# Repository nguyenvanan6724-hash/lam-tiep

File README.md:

# ESP32-C6 audio recorder

| Thư mục / file | Nội dung |
|---|---|
| [`esp32c6_recorder_revC2/`](esp32c6_recorder_revC2/) | **Bản mới nhất.** PCB layout lại 60 × 46 mm, 2 lớp, GND liền lớp dưới. Đọc [README](esp32c6_recorder_revC2/README.md) trước. |
| [`esp32c6_recorder_revC1_goc/`](esp32c6_recorder_revC1_goc/) | Bản gốc rev C1, giữ nguyên để so sánh |
| `Review_schematic_ESP32-C6 (1).pdf`, `esp32_c6_project.pdf` | Tài liệu cũ (review schematic bản trước, bản in schematic cũ) |

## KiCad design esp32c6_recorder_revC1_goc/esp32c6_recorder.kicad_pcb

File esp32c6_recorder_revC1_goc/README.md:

# ESP32-C6 audio recorder – project KiCad 10 (rev C)

Mở `esp32c6_recorder.kicad_pro` bằng KiCad 10 → mở Schematic → **chạy ERC trước** → *Tools → Update PCB from Schematic* (F8).

## Rev C thay đổi gì so với rev B

- **Bỏ CH340C (U11) + mạch tự reset (Q4, Q5, R53–R56, C36, C37).** Nạp code và xem log bằng khối USB Serial/JTAG có sẵn trong ESP32-C6.
- USB-C D+/D− → R70/R71 (22 Ω) → GPIO13/GPIO12. Có chừa chỗ C44/C45 xuống GND (KHÔNG hàn), theo khuyến nghị của Espressif.
- Thẻ SD dời khỏi GPIO12/13: **SD_SCK → GPIO18** (qua R62), **SD_MISO → GPIO19**. SD_CS (IO10) và SD_MOSI (IO11) giữ nguyên.
- UART0 (GPIO16/17) để trống (có cờ no-connect).
- Mọi linh kiện có thêm trường `MPN` và `LCSC` (mã LCSC đã kiểm còn hàng ngày 04/11/2026).
- Net class `USB` có thêm `USB_DP_MCU`, `USB_DM_MCU`.

## Firmware cần chỉnh

- ESP-IDF: `idf.py menuconfig` → Component config → ESP System Settings → Channel for console output = **USB Serial/JTAG**.
- Arduino: Tools → **USB CDC On Boot: Enabled**.
- Firmware treo, ngủ sâu, hoặc lấy IO12/IO13 làm GPIO thì cổng USB sẽ mất. Cách nạp lại: **giữ BOOT, bấm RESET, thả BOOT** để chip vào ROM download, cổng USB sẽ hiện lại.

## File trong project

| File | Nội dung |
|---|---|
| `esp32c6_recorder.kicad_sch` | Schematic rev C (A2) |
| `bom.csv` | BOM gộp: footprint, MPN, **mã LCSC, giá "từ", tồn kho, link** |
| `lib/esp32c6_rec.kicad_sym` | Symbol riêng (vẫn còn symbol CH340C trong thư viện, schematic không dùng nữa) |
| `lib/esp32c6_rec.pretty/` | Footprint riêng: ESP32-C6-WROOM-1, TPS63802 (DLA0010A) |
| `schematic_rev_B_cu.pdf`, `erc_rev_B_cu.rpt` | Bản in và kết quả ERC của **rev B cũ**, giữ lại để so sánh |

## Phải tự kiểm tra

1. **ERC trong KiCad 10.** Rev C được sửa trực tiếp trong file schematic, chưa mở bằng KiCad. Tao đã tự kiểm netlist bằng script (chỉ đổi đúng các net dự kiến, không có dây treo hay nhãn lạc), nhưng vẫn phải chạy ERC thật.
2. In PDF rev C mới: File → Plot.
3. L2: mã mua là Murata **DFE201612E**-R47M, còn footprint đang gán là **DFE201610P**. Hai loại cùng thân 2.0×1.6 mm, nhưng phải so land pattern trong datasheet Murata trước khi đặt PCB.
4. Footprint TPS63802 do Claude tự vẽ theo DLA0010A (TI SLVSEU9D). In tỉ lệ 1:1 và so lại.
5. Khoảng cách 2 hàng chân module INMP441 (J8/J9, J10/J11) phải đo trên module thật.
6. LED 0603: dấu cực tính trên LED LCSC mỗi hãng một kiểu, xem datasheet trước khi hàn.

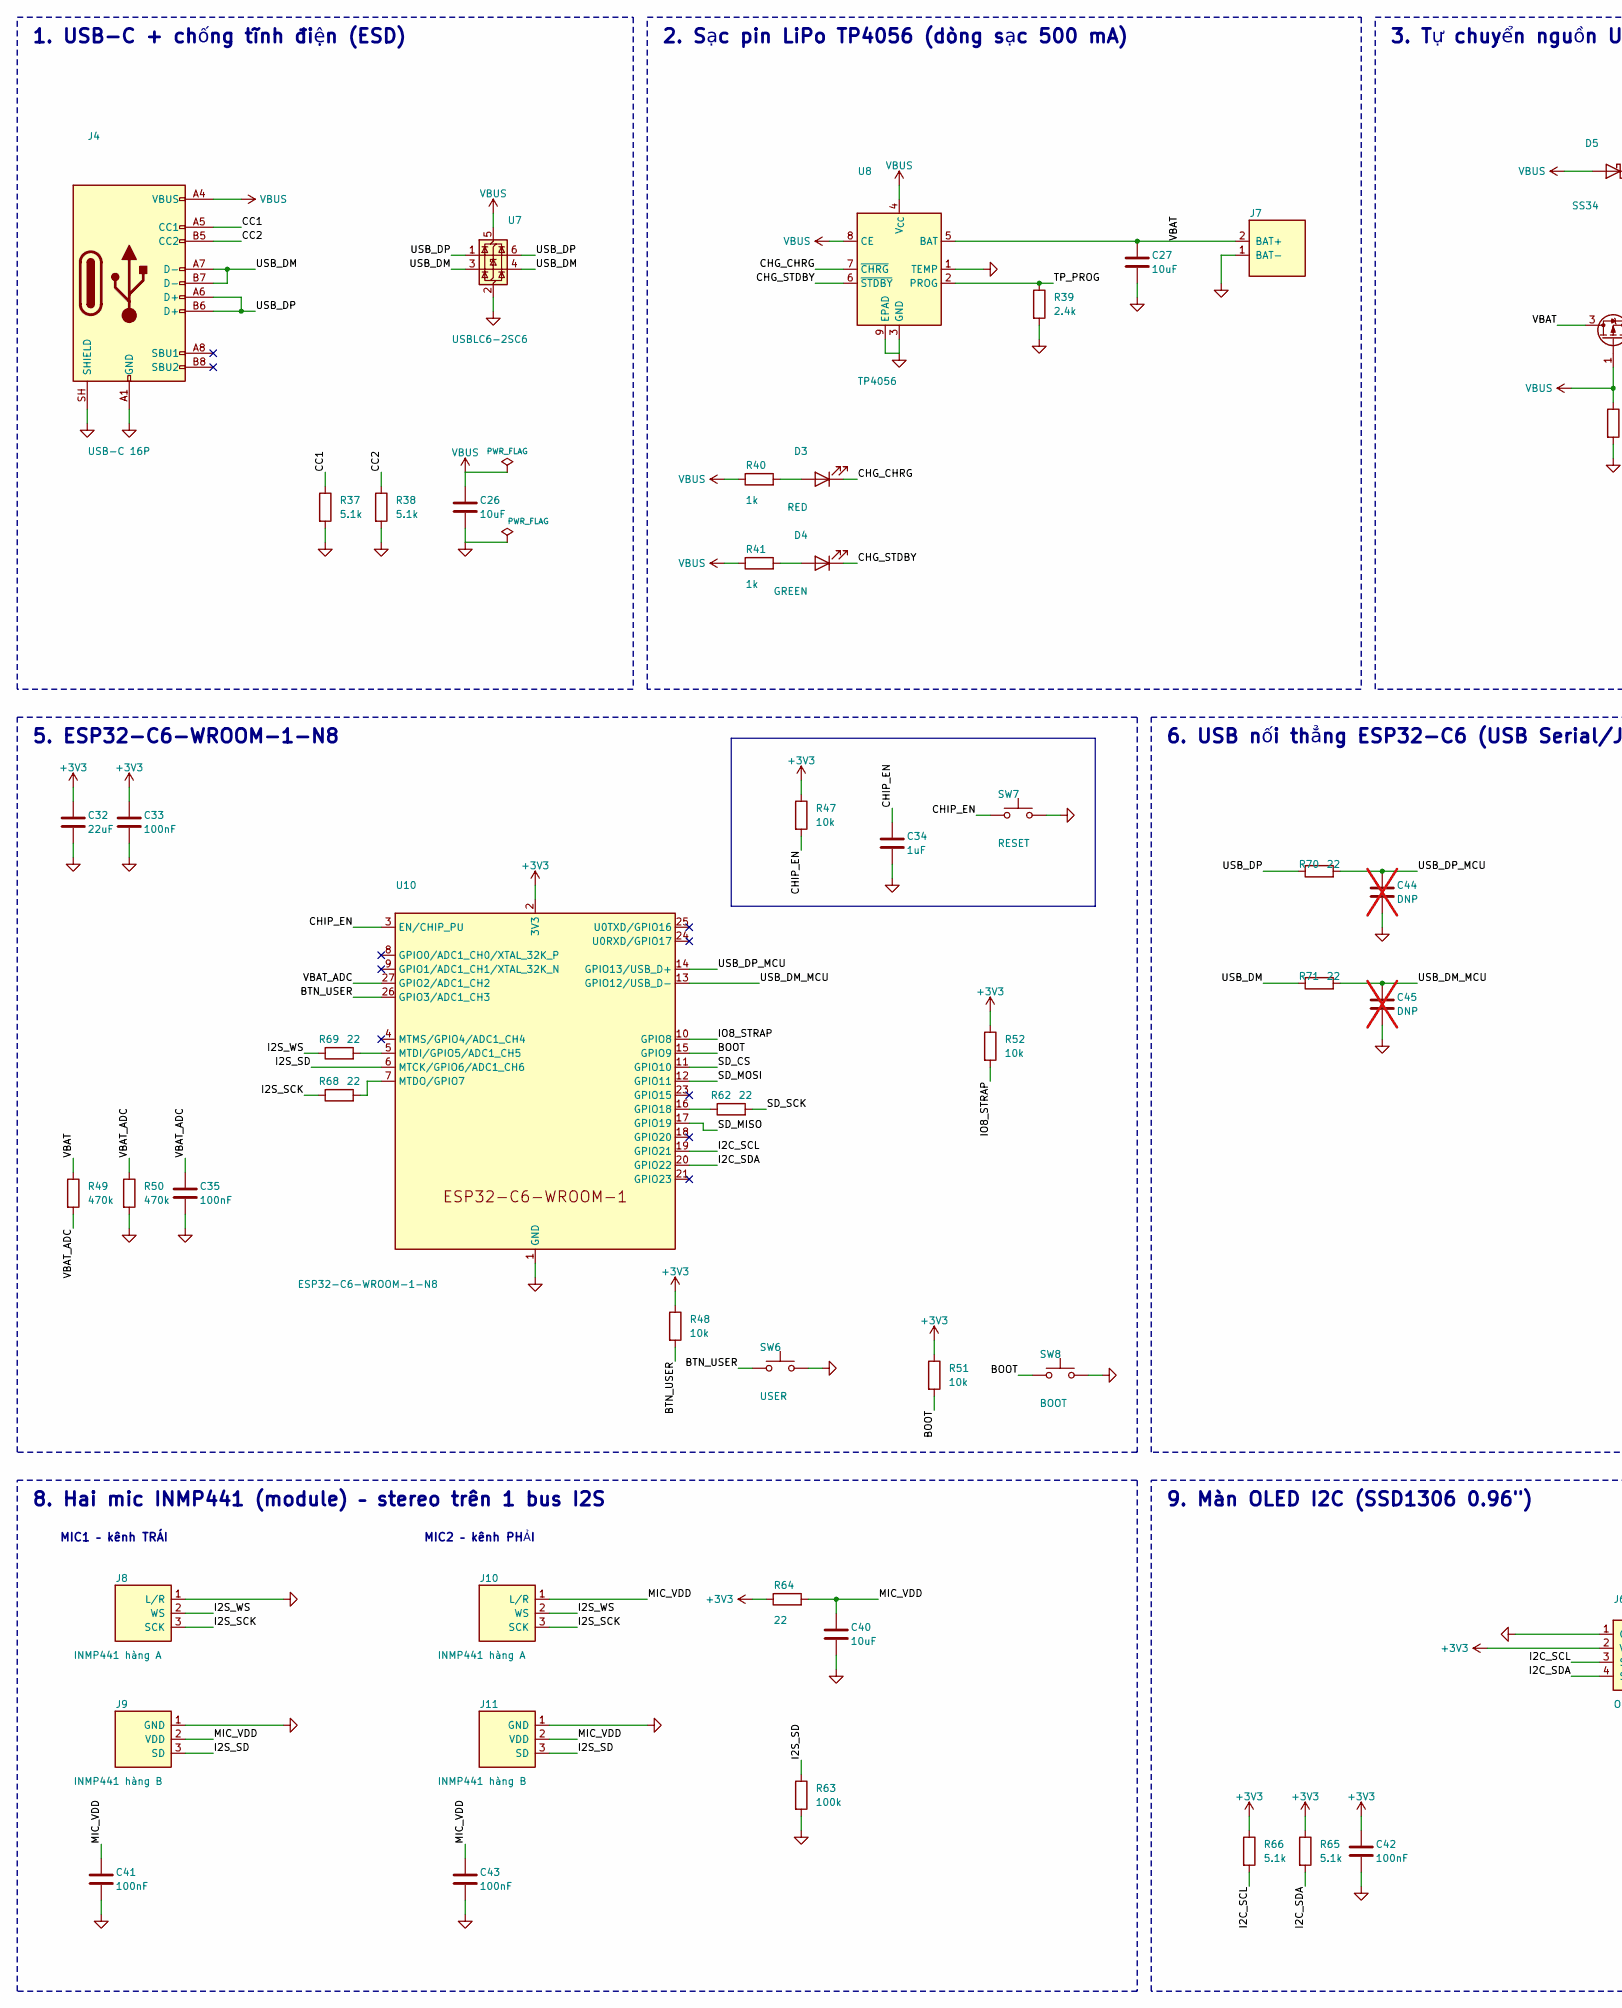
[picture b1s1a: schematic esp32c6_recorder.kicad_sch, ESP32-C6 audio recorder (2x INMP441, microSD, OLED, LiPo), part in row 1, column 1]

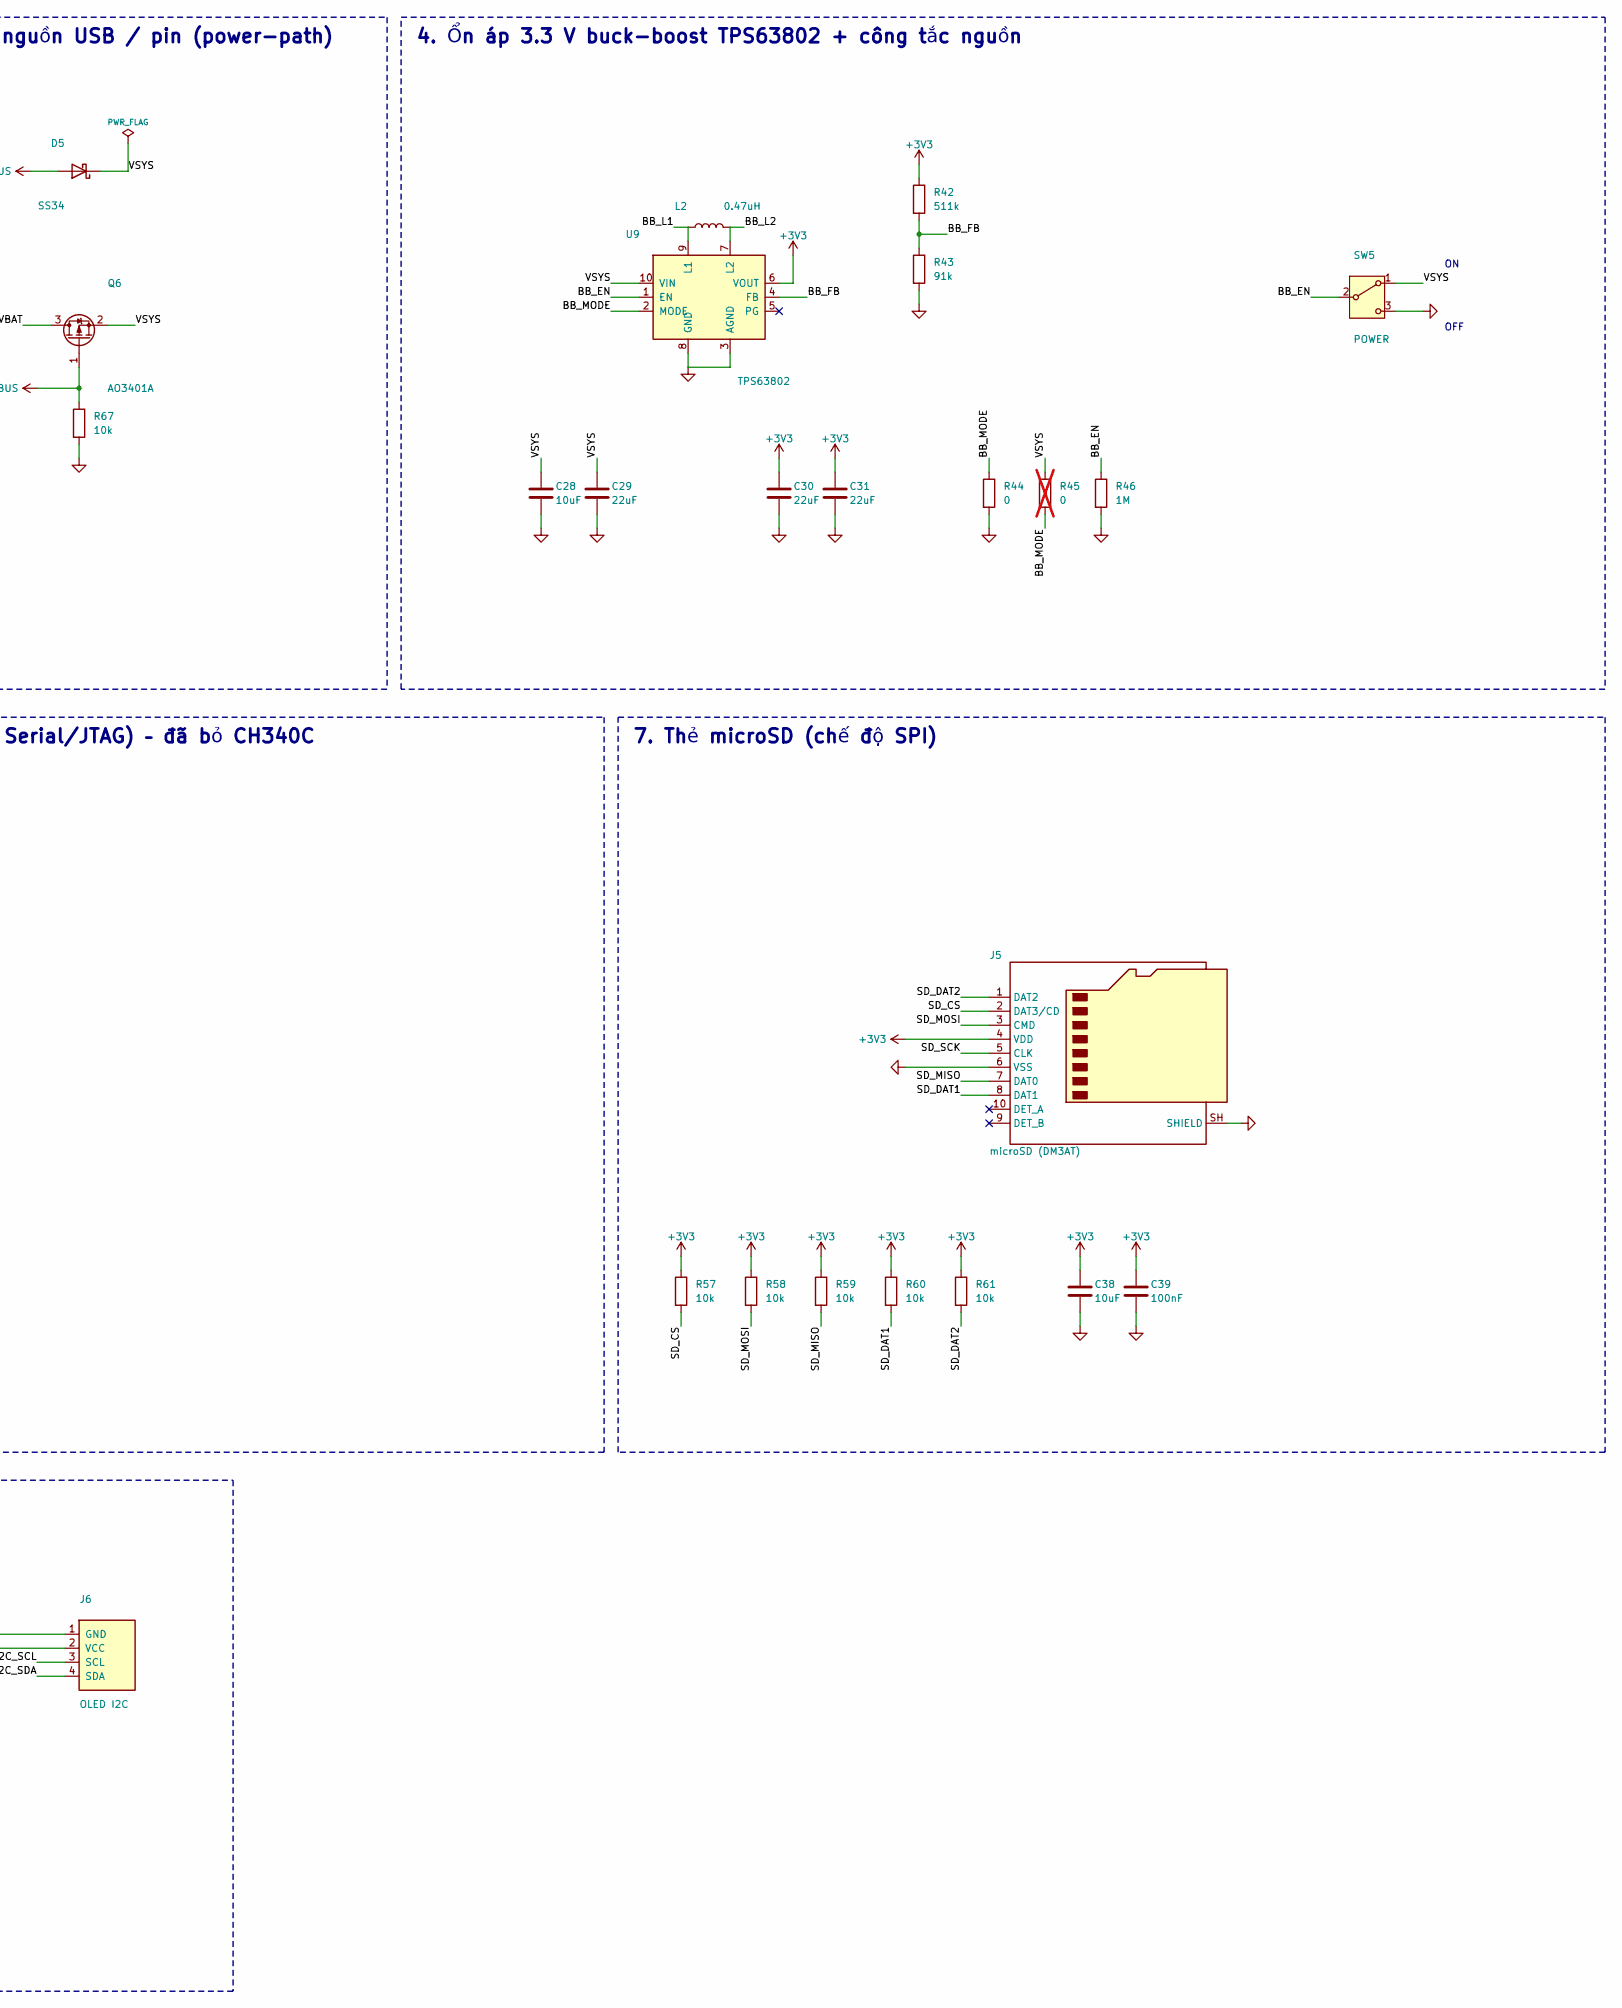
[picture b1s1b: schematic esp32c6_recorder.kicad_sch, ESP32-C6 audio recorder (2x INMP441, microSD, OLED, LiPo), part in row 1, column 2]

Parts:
C26, C27, C38, C40: 10uF; C_0805_2012Metric; MPN Samsung CL21A106KAYNNNE; LCSC C15850
C28: 10uF; C_0603_1608Metric; MPN Samsung CL10A106KP8NNNC; LCSC C19702
C29, C32: 22uF; C_0805_2012Metric; MPN Samsung CL21A226MPQNNNE; LCSC C29277
C30, C31: 22uF; C_0603_1608Metric; MPN Murata GRM188R61A226ME15D; LCSC C84419
C33, C35, C39, C41, C42, C43: 100nF; C_0603_1608Metric; MPN Samsung CL10B104KB8NNNC; LCSC C1591
C34: 1uF; C_0603_1608Metric; MPN Samsung CL10A105KB8NNNC; LCSC C15849
C44, C45: DNP; C_0603_1608Metric; not fitted
D3: RED; LED_0603_1608Metric; MPN KENTO KT-0603R; LCSC C2286
D4: GREEN; LED_0603_1608Metric; MPN KENTO KT-0603G; LCSC C12624
D5: SS34; D_SMA; MPN MDD SS34; LCSC C8678
J4: USB-C 16P; USB_C_Receptacle_HRO_TYPE-C-31-M-12; MPN HRO TYPE-C-31-M-12; LCSC C165948
J5: microSD (DM3AT); microSD_HC_Hirose_DM3AT-SF-PEJM5; MPN Hirose DM3AT-SF-PEJM5; LCSC C114218
J6: OLED I2C; PinSocket_1x04_P2.54mm_Vertical; MPN BOOMELE 2.54-1*4P (header cái); LCSC C2718488
J7: LiPo 1S (có PCM); JST_PH_S2B-PH-K_1x02_P2.00mm_Horizontal; MPN JST S2B-PH-K-S(LF)(SN); LCSC C173752
J8, J10: INMP441 hàng A; PinSocket_1x03_P2.54mm_Vertical; MPN BOOMELE 2.54-1*3P (header cái); LCSC C146243
J9, J11: INMP441 hàng B; PinSocket_1x03_P2.54mm_Vertical; MPN BOOMELE 2.54-1*3P (header cái); LCSC C146243
L2: 0.47uH; L_Murata_DFE201610P; MPN Murata DFE201612E-R47M=P2; LCSC C668312
Q6: AO3401A; SOT-23; MPN AOS AO3401A; LCSC C15127
R37, R38, R65, R66: 5.1k; R_0603_1608Metric; MPN UNI-ROYAL 0603WAF5101T5E; LCSC C23186
R39: 2.4k; R_0603_1608Metric; MPN UNI-ROYAL 0603WAF2401T5E; LCSC C22940
R40, R41: 1k; R_0603_1608Metric; MPN UNI-ROYAL 0603WAF1001T5E; LCSC C21190
R42: 511k; R_0603_1608Metric; MPN UNI-ROYAL 0603WAF5113T5E; LCSC C23194
R43: 91k; R_0603_1608Metric; MPN UNI-ROYAL 0603WAF9102T5E; LCSC C23265
R44: 0; R_0603_1608Metric; MPN UNI-ROYAL 0603WAF0000T5E; LCSC C21189
R45: 0; R_0603_1608Metric; MPN UNI-ROYAL 0603WAF0000T5E; LCSC C21189; not fitted
R46: 1M; R_0603_1608Metric; MPN UNI-ROYAL 0603WAF1004T5E; LCSC C22935
R47, R48, R51, R52, R57, R58, R59, R60, R61, R67: 10k; R_0603_1608Metric; MPN UNI-ROYAL 0603WAF1002T5E; LCSC C25804
R49, R50: 470k; R_0603_1608Metric; MPN UNI-ROYAL 0603WAF4703T5E; LCSC C23178
R62, R64, R68, R69, R70, R71: 22; R_0603_1608Metric; MPN UNI-ROYAL 0603WAF220JT5E; LCSC C23345
R63: 100k; R_0603_1608Metric; MPN UNI-ROYAL 0603WAF1003T5E; LCSC C25803
SW5: POWER; SW_SPDT_Shouhan_MSK12C02; MPN SHOU HAN MSK12C02; LCSC C431540
SW6: USER; SW_Push_1P1T_XKB_TS-1187A; MPN XKB TS-1187A-B-A-B; LCSC C318884
SW7: RESET; SW_Push_1P1T_XKB_TS-1187A; MPN XKB TS-1187A-B-A-B; LCSC C318884
SW8: BOOT; SW_Push_1P1T_XKB_TS-1187A; MPN XKB TS-1187A-B-A-B; LCSC C318884
U7: USBLC6-2SC6; SOT-23-6; MPN ST USBLC6-2SC6; LCSC C7519
U8: TP4056; SOIC-8-1EP_3.9x4.9mm_P1.27mm_EP2.41x3.3mm_ThermalVias; MPN TOPPOWER TP4056-42-ESOP8; LCSC C16581
U9: TPS63802; Texas_DLA0010A_VSON-HR-10_2x3mm_P0.5mm; MPN TI TPS63802DLAR; LCSC C2845237
U10: ESP32-C6-WROOM-1-N8; ESP32-C6-WROOM-1; MPN Espressif ESP32-C6-WROOM-1-N8; LCSC C5366877

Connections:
+3V3: C30.1, C31.1, C32.1, C33.1, C38.1, C39.1, C42.1, J5.4 (VDD), J6.2 (VCC), R42.1, R47.1, R48.1, R51.1, R52.1, R57.1, R58.1, R59.1, R60.1, R61.1, R64.1, R65.1, R66.1, U9.6 (VOUT), U10.2 (3V3)
/BB_EN: R46.1, SW5.2 (B), U9.1 (EN)
/BB_FB: R42.2, R43.1, U9.4 (FB)
/BB_L1: L2.1, U9.9 (L1)
/BB_L2: L2.2, U9.7 (L2)
/BB_MODE: R44.1, R45.2, U9.2 (MODE)
/BOOT: R51.2, SW8.1, U10.15 (GPIO9)
/BTN_USER: R48.2, SW6.1, U10.26 (GPIO3/ADC1_CH3)
/CC1: J4.A5 (CC1), R37.1
/CC2: J4.B5 (CC2), R38.1
/CHG_CHRG: D3.1 (K), U8.7 (~CHRG)
/CHG_STDBY: D4.1 (K), U8.6 (~STDBY)
/CHIP_EN: C34.1, R47.2, SW7.1, U10.3 (EN/CHIP_PU)
/I2C_SCL: J6.3 (SCL), R66.2, U10.19 (GPIO21)
/I2C_SDA: J6.4 (SDA), R65.2, U10.20 (GPIO22)
/I2S_SCK: J8.3 (SCK), J10.3 (SCK), R68.1
/I2S_SD: J9.3 (SD), J11.3 (SD), R63.1, U10.6 (MTCK/GPIO6/ADC1_CH6)
/I2S_WS: J8.2 (WS), J10.2 (WS), R69.1
/IO8_STRAP: R52.2, U10.10 (GPIO8)
/MIC_VDD: C40.1, C41.1, C43.1, J9.2 (VDD), J10.1 (L/R), J11.2 (VDD), R64.2
/SD_CS: J5.2 (DAT3/CD), R57.2, U10.11 (GPIO10)
/SD_DAT1: J5.8 (DAT1), R60.2
/SD_DAT2: J5.1 (DAT2), R61.2
/SD_MISO: J5.7 (DAT0), R59.2, U10.17 (GPIO19)
/SD_MOSI: J5.3 (CMD), R58.2, U10.12 (GPIO11)
/SD_SCK: J5.5 (CLK), R62.2
/TP_PROG: R39.1, U8.2 (PROG)
/USB_DM: J4.A7 (D-), J4.B7 (D-), R71.1, U7.3 (I/O2), U7.4 (I/O2)
/USB_DM_MCU: C45.1, R71.2, U10.13 (GPIO12/USB_D-)
/USB_DP: J4.A6 (D+), J4.B6 (D+), R70.1, U7.1 (I/O1), U7.6 (I/O1)
/USB_DP_MCU: C44.1, R70.2, U10.14 (GPIO13/USB_D+)
/VBAT: C27.1, J7.2 (BAT+), Q6.3 (D), R49.1, U8.5 (BAT)
/VBAT_ADC: C35.1, R49.2, R50.1, U10.27 (GPIO2/ADC1_CH2)
/VSYS: C28.1, C29.1, D5.1 (K), Q6.2 (S), R45.1, SW5.1 (A), U9.10 (VIN)
GND: C26.2, C27.2, C28.2, C29.2, C30.2, C31.2, C32.2, C33.2, C34.2, C35.2, C38.2, C39.2, C40.2, C41.2, C42.2, C43.2, C44.2, C45.2, J4.A1 (GND), J4.A12 (GND), J4.B1 (GND), J4.B12 (GND), J4.SH (SHIELD), J5.6 (VSS), J5.SH (SHIELD), J6.1 (GND), J7.1 (BAT-), J8.1 (L/R), J9.1 (GND), J11.1 (GND), R37.2, R38.2, R39.2, R43.2, R44.2, R46.2, R50.2, R63.2, R67.2, SW5.3 (C), SW6.2, SW7.2, SW8.2, U7.2 (GND), U8.1 (TEMP), U8.3 (GND), U8.9 (EPAD), U9.3 (AGND), U9.8 (GND), U10.1 (GND), U10.28 (GND), U10.29 (GND)
unnamed: D3.2 (A), R40.2
unnamed: D4.2 (A), R41.2
unnamed: R62.1, U10.16 (GPIO18)
unnamed: R69.2, U10.5 (MTDI/GPIO5/ADC1_CH5)
unnamed: R68.2, U10.7 (MTDO/GPIO7)
VBUS: C26.1, D5.2 (A), J4.A4 (VBUS), J4.A9 (VBUS), J4.B4 (VBUS), J4.B9 (VBUS), Q6.1 (G), R40.1, R41.1, R67.1, U7.5 (VBUS), U8.4 (V_{CC}), U8.8 (CE)

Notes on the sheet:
1. USB-C + chống tĩnh điện (ESD)
5. ESP32-C6-WROOM-1-N8
MIC2 – kênh PHẢI
8. Hai mic INMP441 (module) – stereo trên 1 bus I2S
2. Sạc pin LiPo TP4056 (dòng sạc 500 mA)
OFF
3. Tự chuyển nguồn USB / pin (power-path)
6. USB nối thẳng ESP32-C6 (USB Serial/JTAG) – đã bỏ CH340C
7. Thẻ microSD (chế độ SPI)
4. Ổn áp 3.3 V buck-boost TPS63802 + công tắc nguồn
9. Màn OLED I2C (SSD1306 0.96")
MIC1 – kênh TRÁI

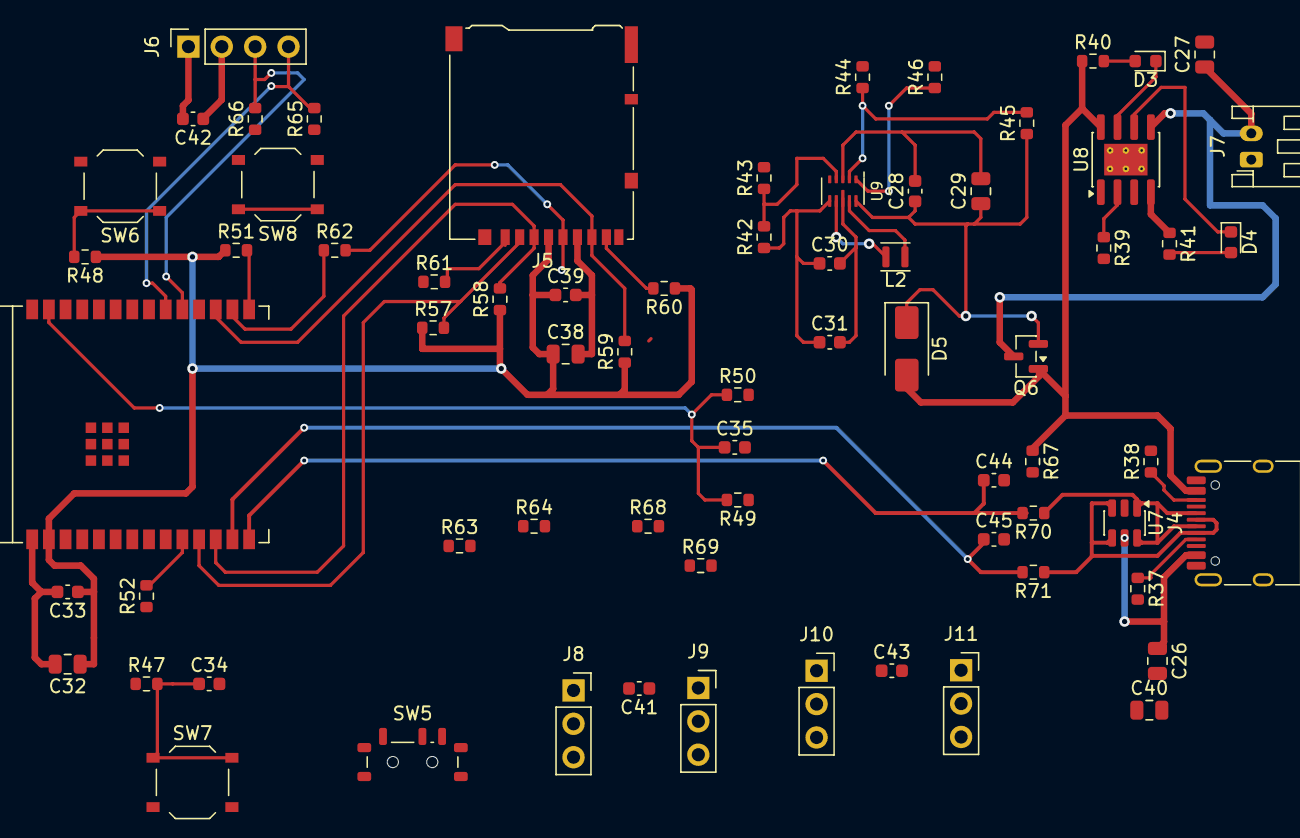
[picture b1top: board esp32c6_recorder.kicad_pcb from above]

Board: 2 copper layers, 70 parts (0 on the bottom side), 41 nets.

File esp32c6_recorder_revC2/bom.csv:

"Ref","Value","Footprint","Spec","MPN","LCSC","Qty","DNP","Gia_tu_USD","Ton_kho_04-11-2026","Link","Note"
"C26,C27,C38,C40","10uF","Capacitor_SMD:C_0805_2012Metric","25V X5R","Samsung CL21A106KAYNNNE","C15850","4","","0.024","875380","https://www.lcsc.com/product-detail/C15850.html","Đặt sát chân VCC của U8 (TP4056); Sát chân BAT; Sát chân VDD (4) của khe thẻ"
"C28","10uF","Capacitor_SMD:C_0603_1608Metric","10V X5R","Samsung CL10A106KP8NNNC","C19702","1","","0.0108","1692360","https://www.lcsc.com/product-detail/C19702.html","Sát chân VIN (10) – GND (8)"
"C29,C32","22uF","Capacitor_SMD:C_0805_2012Metric","10V X5R","Samsung CL21A226MPQNNNE","C29277","2","","0.0202","472450","https://www.lcsc.com/product-detail/C29277.html","Sát chân 3V3 (pin 2) của module"
"C30,C31","22uF","Capacitor_SMD:C_0603_1608Metric","10V X5R","Murata GRM188R61A226ME15D","C84419","2","","0.1153","590775","https://www.lcsc.com/product-detail/C84419.html","Sát chân VOUT (6)"
"C33,C35,C39,C41-C43","100nF","Capacitor_SMD:C_0603_1608Metric","","Samsung CL10B104KB8NNNC","C1591","6","","0.004","1205600","https://www.lcsc.com/product-detail/C1591.html","Sát chân 3V3 (pin 2); Sát chân IO2; Sát chân VDD (4); Sát header MIC1; Sát header OLED; Sát header MIC2"
"C34","1uF","Capacitor_SMD:C_0603_1608Metric","","Samsung CL10A105KB8NNNC","C15849","1","","0.0079","583750","https://www.lcsc.com/product-detail/C15849.html","EN: τ = 10k × 1µF = 10 ms"
"C44,C45","DNP","Capacitor_SMD:C_0603_1608Metric","","","","2","DNP","","","","DNP – chỉ chừa chỗ (Espressif khuyến nghị)"
"D3","RED","LED_SMD:LED_0603_1608Metric","","KENTO KT-0603R","C2286","1","","0.0036","4254200","https://www.lcsc.com/product-detail/C2286.html","Sáng = đang sạc"
"D4","GREEN","LED_SMD:LED_0603_1608Metric","","KENTO KT-0603G","C12624","1","","0.0058","362900","https://www.lcsc.com/product-detail/C12624.html","Sáng = sạc đầy (Vf ≈ 3.1 V)"
"D5","SS34","Diode_SMD:D_SMA","","MDD SS34","C8678","1","","0.0157","2368940","https://www.lcsc.com/product-detail/C8678.html","Schottky ≥ 1 A"
"J4","USB-C 16P","Connector_USB:USB_C_Receptacle_HRO_TYPE-C-31-M-12","","HRO TYPE-C-31-M-12","C165948","1","","0.0975","149550","https://www.lcsc.com/product-detail/C165948.html","Đối chiếu đúng mã đầu cắm trước khi làm PCB"
"J5","microSD (DM3AT)","Connector_Card:microSD_HC_Hirose_DM3AT-SF-PEJM5","","Hirose DM3AT-SF-PEJM5","C114218","1","","0.7741","17934","https://www.lcsc.com/product-detail/C114218.html","Nếu đổi khe thẻ khác thì đổi cả footprint"
"J6","OLED I2C","Connector_PinSocket_2.54mm:PinSocket_1x04_P2.54mm_Vertical","","BOOMELE 2.54-1*4P (header cái)","C2718488","1","","0.0413","112510","https://www.lcsc.com/product-detail/C2718488.html","Kiểm thứ tự chân: có module đảo VCC/GND"
"J7","LiPo 1S (có PCM)","Connector_JST:JST_PH_S2B-PH-K_1x02_P2.00mm_Horizontal","","JST S2B-PH-K-S(LF)(SN)","C173752","1","","0.0213","195880","https://www.lcsc.com/product-detail/C173752.html","Đo cực tính dây pin trước khi cắm"
"J8,J10","INMP441 hàng A","Connector_PinSocket_2.54mm:PinSocket_1x03_P2.54mm_Vertical","","BOOMELE 2.54-1*3P (header cái)","C146243","2","","0.0654","27210","https://www.lcsc.com/product-detail/C146243.html","Đối chiếu thứ tự chân và đo khoảng cách 2 hàng chân của module"
"J9,J11","INMP441 hàng B","Connector_PinSocket_2.54mm:PinSocket_1x03_P2.54mm_Vertical","","BOOMELE 2.54-1*3P (header cái)","C146243","2","","0.0654","27210","https://www.lcsc.com/product-detail/C146243.html","Đối chiếu thứ tự chân module"
"L2","0.47uH","Inductor_SMD:L_Murata_DFE201610P","Isat ≥ 4 A, DCR ≤ 30 mΩ","Murata DFE201612E-R47M=P2","C668312","1","","0.115","8525","https://www.lcsc.com/product-detail/C668312.html",""
"Q6","AO3401A","Package_TO_SOT_SMD:SOT-23","","AOS AO3401A","C15127","1","","0.0579","1194320","https://www.lcsc.com/product-detail/C15127.html","D ở phía pin, S ở phía tải (bắt buộc đúng chiều)"
"R37,R38,R65,R66","5.1k","Resistor_SMD:R_0603_1608Metric","1%","UNI-ROYAL 0603WAF5101T5E","C23186","4","","0.0007","15598900","https://www.lcsc.com/product-detail/C23186.html","Module đã có pull-up thì có thể bỏ (DNP)"
"R39","2.4k","Resistor_SMD:R_0603_1608Metric","1%","UNI-ROYAL 0603WAF2401T5E","C22940","1","","0.0014","877400","https://www.lcsc.com/product-detail/C22940.html","I_sạc = 1200 V / R39 = 0.5 A. Chọn lại theo dung lượng pin"
"R40,R41","1k","Resistor_SMD:R_0603_1608Metric","","UNI-ROYAL 0603WAF1001T5E","C21190","2","","0.0009","3451500","https://www.lcsc.com/product-detail/C21190.html",""
"R42","511k","Resistor_SMD:R_0603_1608Metric","1%","UNI-ROYAL 0603WAF5113T5E","C23194","1","","0.0016","25300","https://www.lcsc.com/product-detail/C23194.html",""
"R43","91k","Resistor_SMD:R_0603_1608Metric","1%","UNI-ROYAL 0603WAF9102T5E","C23265","1","","0.0022","73700","https://www.lcsc.com/product-detail/C23265.html",""
"R44","0","Resistor_SMD:R_0603_1608Metric","","UNI-ROYAL 0603WAF0000T5E","C21189","1","","0.0012","11031300","https://www.lcsc.com/product-detail/C21189.html","MODE thấp = tiết kiệm (PFM)"
"R45","0","Resistor_SMD:R_0603_1608Metric","","UNI-ROYAL 0603WAF0000T5E","C21189","1","DNP","0.0012","11031300","https://www.lcsc.com/product-detail/C21189.html","DNP. Hàn R45 + bỏ R44 = PWM cố định (ít nhiễu âm thanh)"
"R46","1M","Resistor_SMD:R_0603_1608Metric","","UNI-ROYAL 0603WAF1004T5E","C22935","1","","0.0009","1742900","https://www.lcsc.com/product-detail/C22935.html","Giữ EN thấp khi công tắc đang chuyển"
"R47,R48,R51,R52,R57-R61,R67","10k","Resistor_SMD:R_0603_1608Metric","","UNI-ROYAL 0603WAF1002T5E","C25804","10","","0.0016","5673300","https://www.lcsc.com/product-detail/C25804.html","GPIO8 phải = 1 khi vào chế độ nạp; Kéo gate xuống khi rút USB"
"R49,R50","470k","Resistor_SMD:R_0603_1608Metric","1%","UNI-ROYAL 0603WAF4703T5E","C23178","2","","0.0014","427700","https://www.lcsc.com/product-detail/C23178.html",""
"R62,R64,R68-R71","22","Resistor_SMD:R_0603_1608Metric","","UNI-ROYAL 0603WAF220JT5E","C23345","6","","0.001","2808700","https://www.lcsc.com/product-detail/C23345.html","Sát chân ESP32 – SD_SCK (IO18); Lọc RC nguồn mic; Sát chân ESP32; USB D+ → GPIO13, đặt SÁT chân ESP32; USB D− → GPIO12, đặt SÁT chân ESP32"
"R63","100k","Resistor_SMD:R_0603_1608Metric","","UNI-ROYAL 0603WAF1003T5E","C25803","1","","0.0015","8006000","https://www.lcsc.com/product-detail/C25803.html","Kéo xuống đường SD (datasheet)"
"SW5","POWER","Button_Switch_SMD:SW_SPDT_Shouhan_MSK12C02","","SHOU HAN MSK12C02","C431540","1","","0.0305","168360","https://www.lcsc.com/product-detail/C431540.html",""
"SW6","USER","Button_Switch_SMD:SW_Push_1P1T_XKB_TS-1187A","","XKB TS-1187A-B-A-B","C318884","1","","0.0112","767160","https://www.lcsc.com/product-detail/C318884.html",""
"SW7","RESET","Button_Switch_SMD:SW_Push_1P1T_XKB_TS-1187A","","XKB TS-1187A-B-A-B","C318884","1","","0.0112","767160","https://www.lcsc.com/product-detail/C318884.html",""
"SW8","BOOT","Button_Switch_SMD:SW_Push_1P1T_XKB_TS-1187A","","XKB TS-1187A-B-A-B","C318884","1","","0.0112","767160","https://www.lcsc.com/product-detail/C318884.html",""
"U7","USBLC6-2SC6","Package_TO_SOT_SMD:SOT-23-6","","ST USBLC6-2SC6","C7519","1","","0.0932","37330","https://www.lcsc.com/product-detail/C7519.html","Đặt sát cổng USB"
"U8","TP4056","Package_SO:SOIC-8-1EP_3.9x4.9mm_P1.27mm_EP2.41x3.3mm_ThermalVias","","TOPPOWER TP4056-42-ESOP8","C16581","1","","0.0895","53010","https://www.lcsc.com/product-detail/C16581.html","Pad tản nhiệt (EPAD) hàn xuống GND + via"
"U9","TPS63802","esp32c6_rec:Texas_DLA0010A_VSON-HR-10_2x3mm_P0.5mm","","TI TPS63802DLAR","C2845237","1","","0.5383","26562","https://www.lcsc.com/product-detail/C2845237.html","Footprint tự vẽ theo land pattern DLA0010A, kiểm lại trước khi đặt mạch"
"U10","ESP32-C6-WROOM-1-N8","esp32c6_rec:ESP32-C6-WROOM-1","","Espressif ESP32-C6-WROOM-1-N8","C5366877","1","","2.976","5384","https://www.lcsc.com/product-detail/C5366877.html","Ăng-ten ra mép board, cấm đồng dưới ăng-ten"
